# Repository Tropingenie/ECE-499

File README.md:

# ECE-499
[Nozzle Flow Control for Agricultural Integration](https://tropingenie.github.io/ECE-499-Website/)

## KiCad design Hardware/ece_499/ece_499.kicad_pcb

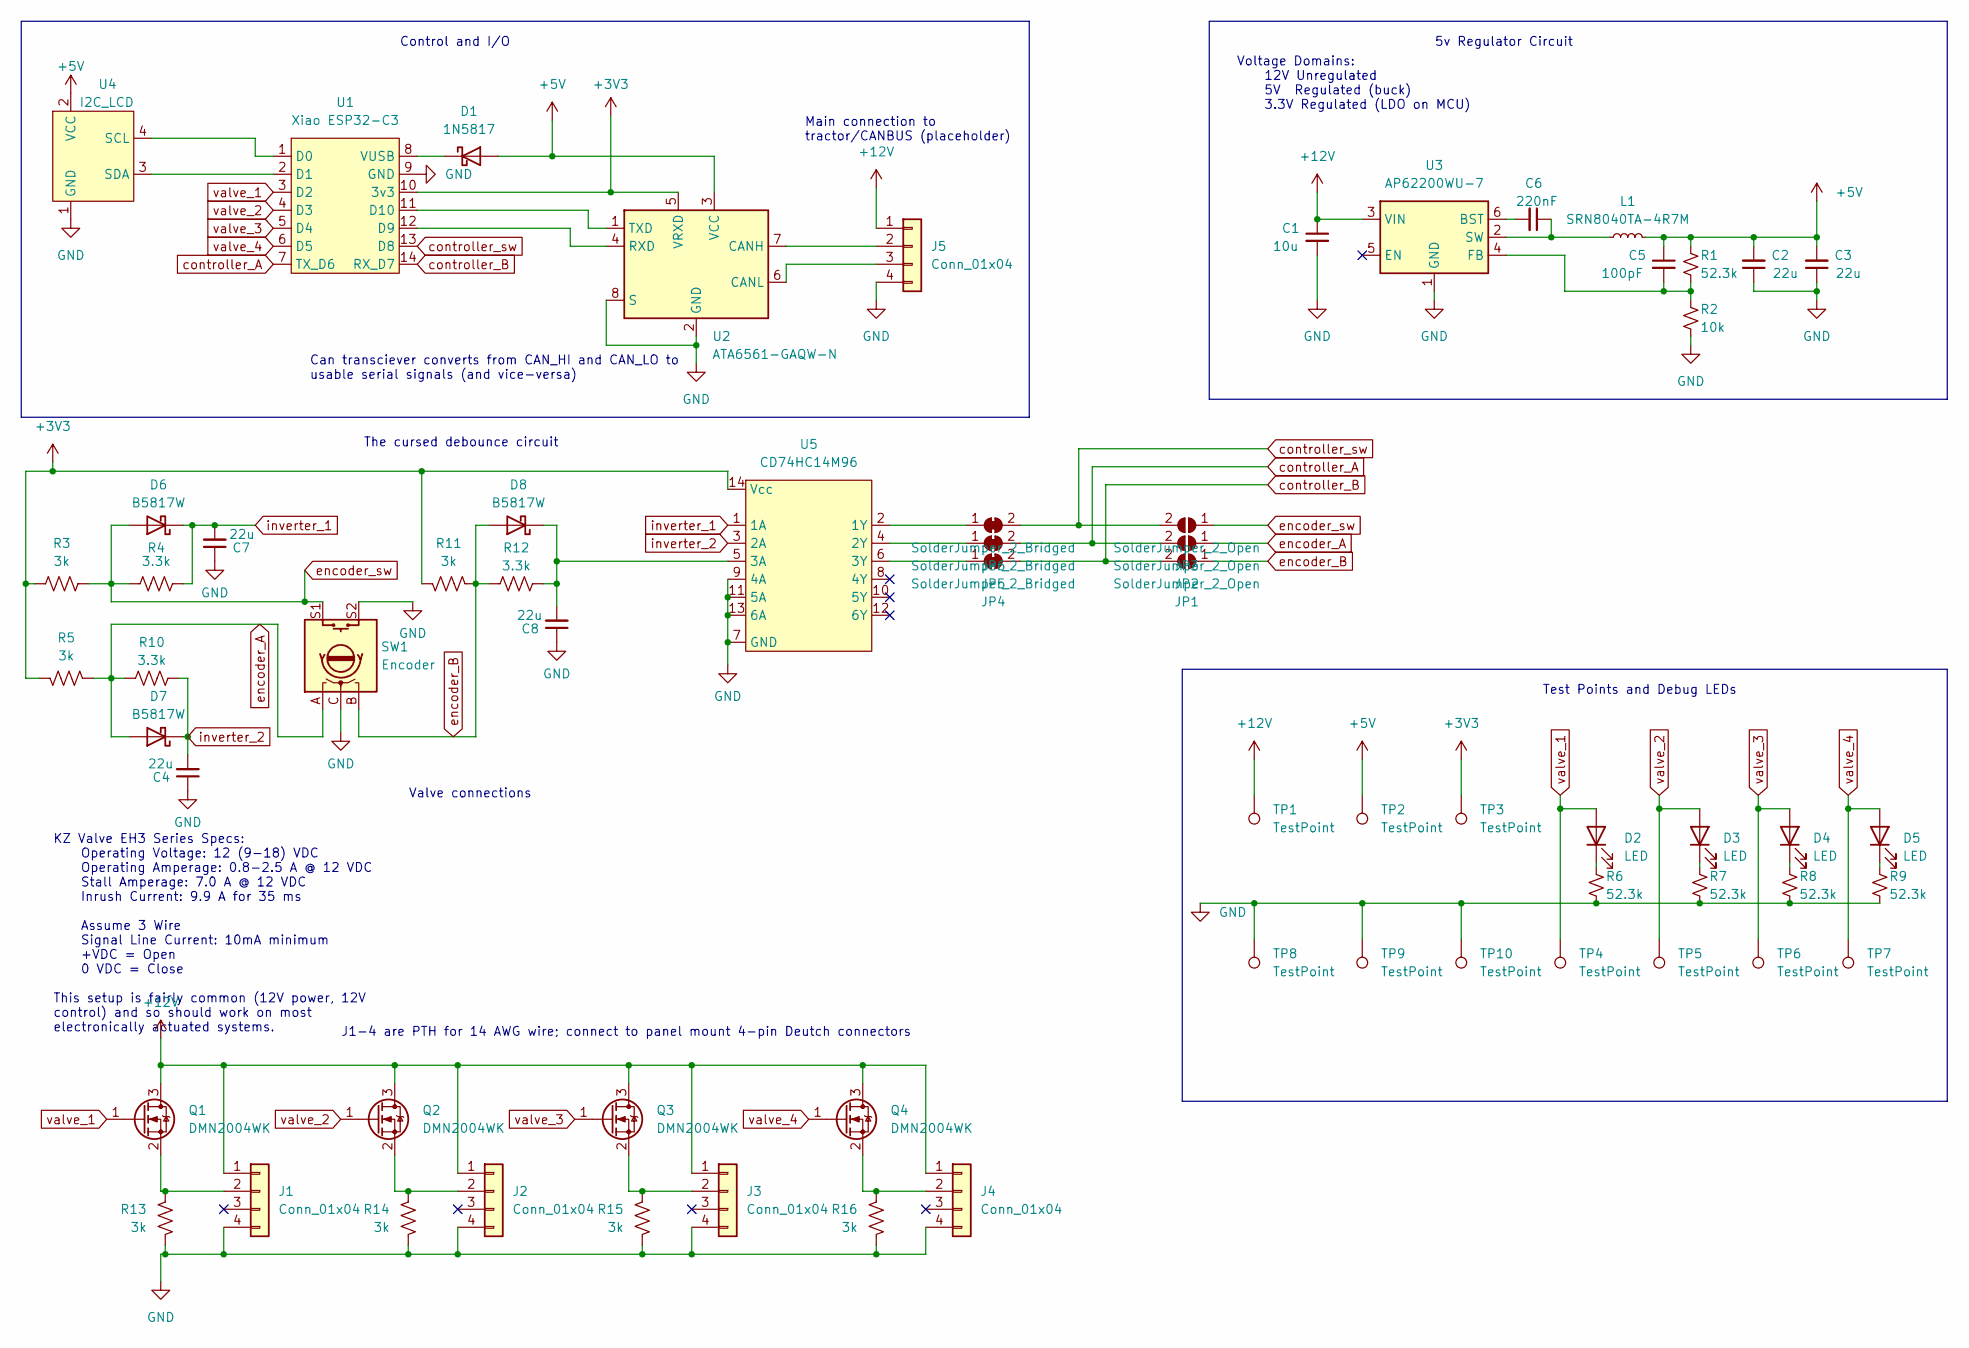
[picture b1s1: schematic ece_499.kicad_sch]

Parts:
C1: 10u; C_0805_2012Metric_Pad1.18x1.45mm_HandSolder
C2, C3, C4, C7, C8: 22u; C_0805_2012Metric_Pad1.18x1.45mm_HandSolder
C5: 100pF; C_0805_2012Metric_Pad1.18x1.45mm_HandSolder
C6: 220nF; C_0805_2012Metric_Pad1.18x1.45mm_HandSolder
D1: 1N5817; D_A-405_P7.62mm_Horizontal
D2, D3, D4, D5: LED; LED_D5.0mm
D6, D7, D8: B5817W; D_SOD-123
J1, J2, J3, J4, J5: Conn_01x04; 14 AWG 01x04
JP1, JP2, JP3: SolderJumper_2_Open; SolderJumper-2_P1.3mm_Open_RoundedPad1.0x1.5mm
JP4, JP5, JP6: SolderJumper_2_Bridged; SolderJumper-2_P1.3mm_Bridged2Bar_RoundedPad1.0x1.5mm
L1: SRN8040TA-4R7M; IND_SRN8040TA-4R7M
Q1, Q2, Q3, Q4: DMN2004WK; SOT-323_SC-70
R1: 52.3k; R_1206_3216Metric_Pad1.30x1.75mm_HandSolder
R2: 10k; R_1206_3216Metric_Pad1.30x1.75mm_HandSolder
R3, R5, R11, R13, R14, R15, R16: 3k; R_1206_3216Metric_Pad1.30x1.75mm_HandSolder
R4, R10, R12: 3.3k; R_1206_3216Metric_Pad1.30x1.75mm_HandSolder
R6, R7, R8, R9: 52.3k; R_Axial_DIN0204_L3.6mm_D1.6mm_P5.08mm_Horizontal
SW1: Encoder; PEC16-4015F-S0024
TP1, TP2, TP3, TP4, TP5, TP6, TP7, TP8, TP9, TP10: TestPoint; TestPoint_Pad_D2.0mm
U1: Xiao ESP32-C3; XIAO ESP32-C3
U2: ATA6561-GAQW-N; SOIC-8_3.9x4.9mm_P1.27mm
U3: AP62200WU-7; SOT-23-6_Handsoldering
U4: I2C_LCD; PinHeader_1x06_P1.00mm_Horizontal
U5: CD74HC14M96; SO-14_3.9x8.65mm_P1.27mm

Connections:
+3V3: R3.1, R5.1, R11.1, TP3.1, U1.10 (3v3), U2.5 (VRXD), U5.14 (Vcc)
+5V: C2.2, C3.2, C5.1, D1.2 (A), L1.2, R1.1, TP2.1, U2.3 (VCC), U4.2 (VCC)
+12V: C1.1, J1.1, J2.1, J3.1, J4.1, J5.1, Q1.3 (D), Q2.3 (D), Q3.3 (D), Q4.3 (D), TP1.1, U3.3 (VIN)
GND: C1.2, C2.1, C3.1, C4.1, C7.1, C8.1, J1.4, J2.4, J3.4, J4.4, J5.4, R2.2, R6.2, R7.2, R8.2, R9.2, R13.1, R14.1, R15.1, R16.1, SW1.C, SW1.S2, TP8.1, TP9.1, TP10.1, U1.9 (GND), U2.2 (GND), U2.8 (S), U3.1 (GND), U4.1 (GND), U5.7 (GND), U5.9 (4A), U5.11 (5A), U5.13 (6A)
unnamed: D1.1 (K), U1.8 (VUSB)
unnamed: D2.1 (K), R6.1
unnamed: D3.1 (K), R7.1
unnamed: D4.1 (K), R8.1
unnamed: D5.1 (K), R9.1
unnamed: C8.2, D8.1 (K), R12.1, U5.5 (3A)
unnamed: J1.2, Q1.2 (S), R13.2
unnamed: J2.2, Q2.2 (S), R14.2
unnamed: J3.2, Q3.2 (S), R15.2
unnamed: J4.2, Q4.2 (S), R16.2
unnamed: J5.2, U2.7 (CANH)
unnamed: J5.3, U2.6 (CANL)
unnamed: JP4.1 (A), U5.6 (3Y)
unnamed: JP5.1 (A), U5.4 (2Y)
unnamed: JP6.1 (A), U5.2 (1Y)
unnamed: U1.1 (D0), U4.4 (SCL)
unnamed: U1.2 (D1), U4.3 (SDA)
unnamed: U1.12 (D9), U2.4 (RXD)
unnamed: U1.11 (D10), U2.1 (TXD)
unnamed: C6.2, U3.6 (BST)
unnamed: C5.2, R1.2, R2.1, U3.4 (FB)
unnamed: C6.1, L1.1, U3.2 (SW)
controller_A: JP2.2 (B), JP5.2 (B), U1.7 (TX_D6)
controller_B: JP1.2 (B), JP4.2 (B), U1.14 (RX_D7)
controller_sw: JP3.2 (B), JP6.2 (B), U1.13 (D8)
encoder_A: D7.2 (A), JP2.1 (A), R5.2, R10.2, SW1.A
encoder_B: D8.2 (A), JP1.1 (A), R11.2, R12.2, SW1.B
encoder_sw: D6.2 (A), JP3.1 (A), R3.2, R4.2, SW1.S1
inverter_1: C7.2, D6.1 (K), R4.1, U5.1 (1A)
inverter_2: C4.2, D7.1 (K), R10.1, U5.3 (2A)
valve_1: D2.2 (A), Q1.1 (G), TP4.1, U1.3 (D2)
valve_2: D3.2 (A), Q2.1 (G), TP5.1, U1.4 (D3)
valve_3: D4.2 (A), Q3.1 (G), TP6.1, U1.5 (D4)
valve_4: D5.2 (A), Q4.1 (G), TP7.1, U1.6 (D5)

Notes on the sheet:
Valve connections
5v Regulator Circuit
KZ Valve EH3 Series Specs: Operating Voltage: 12 (9-18) VDC Operating Amperage: 0.8-2.5 A @ 12 VDC Stall Amperage: 7.0 A @ 12 VDC Inrush Current: 9.9 A for 35 ms Assume 3 Wire Signal Line Current: 10mA minimum +VDC = Open 0 VDC = Close This setup is fairly common (12V power, 12V control) and so sho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
Control and I/O
Voltage Domains: 12V Unregulated 5V Regulated (buck) 3.3V Regulated (LDO on MCU)
The cursed debounce circuit
Can transciever converts from CAN_HI and CAN_LO to usable serial signals (and vice-versa)
Main connection to tractor/CANBUS (placeholder)
J1-4 are PTH for 14 AWG wire; connect to panel mount 4-pin Deutch connectors
Test Points and Debug LEDs

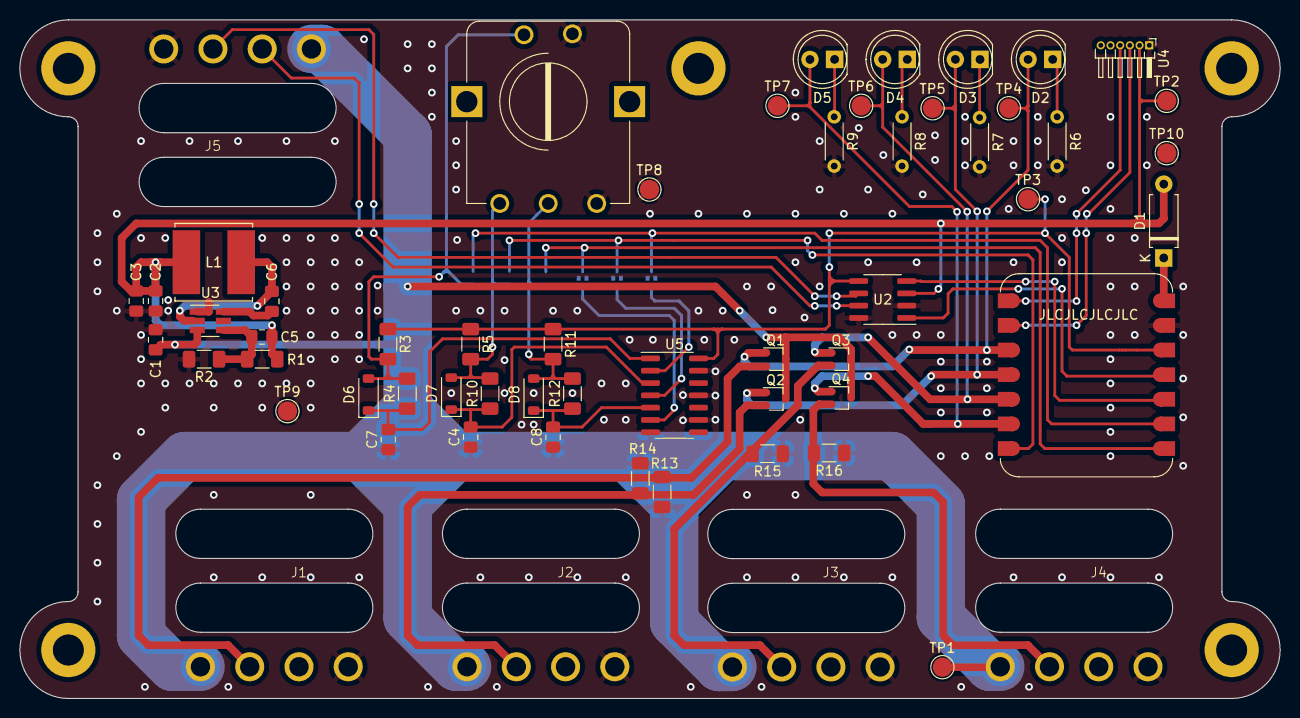
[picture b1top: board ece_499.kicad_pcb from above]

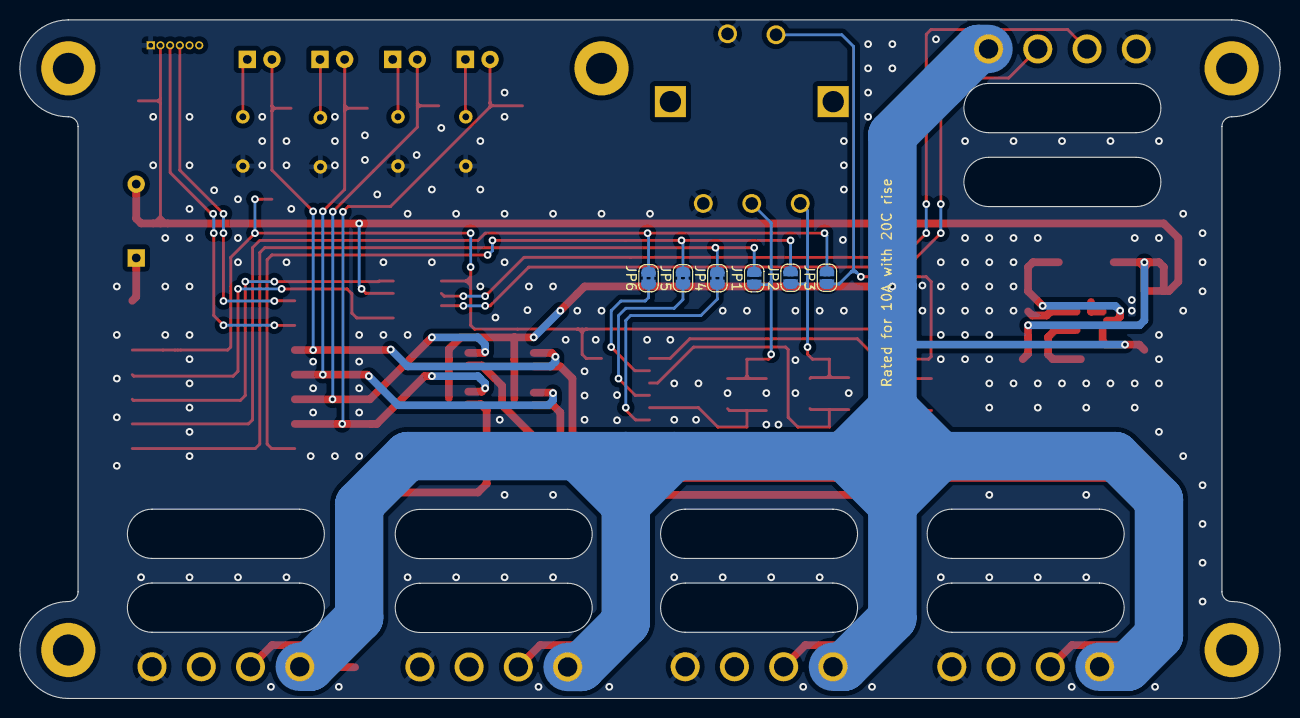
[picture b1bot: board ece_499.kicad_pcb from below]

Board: 2 copper layers, 130.0 x 70.0 mm, 64 parts (6 on the bottom side), 38 nets.

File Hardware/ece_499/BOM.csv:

"Reference","Value","Datasheet","Footprint","Qty","DNP"
"C1","10u","~","Capacitor_SMD:C_0805_2012Metric_Pad1.18x1.45mm_HandSolder","1",""
"C2,C3,C4,C7,C8","22u","~","Capacitor_SMD:C_0805_2012Metric_Pad1.18x1.45mm_HandSolder","5",""
"C5","100pF","~","Capacitor_SMD:C_0805_2012Metric_Pad1.18x1.45mm_HandSolder","1",""
"C6","220nF","~","Capacitor_SMD:C_0805_2012Metric_Pad1.18x1.45mm_HandSolder","1",""
"D1","1N5817","https://www.smc-diodes.com/propdf/B5817W-B5819W%20N1752%20REV.-.pdf","Diode_THT:D_A-405_P7.62mm_Horizontal","1",""
"D2,D3,D4,D5","LED","~","LED_THT:LED_D5.0mm","4",""
"D6,D7,D8","B5817W","https://www.smc-diodes.com/propdf/B5817W-B5819W%20N1752%20REV.-.pdf","Diode_SMD:D_SOD-123","3",""
"J1,J2,J3,J4,J5","Conn_01x04","~","Imported_Parts:14 AWG 01x04","5",""
"JP1,JP2,JP3","SolderJumper_2_Open","~","Jumper:SolderJumper-2_P1.3mm_Open_RoundedPad1.0x1.5mm","3",""
"JP4,JP5,JP6","SolderJumper_2_Bridged","~","Jumper:SolderJumper-2_P1.3mm_Bridged2Bar_RoundedPad1.0x1.5mm","3",""
"L1","SRN8040TA-4R7M","~","Imported_Parts:IND_SRN8040TA-4R7M","1",""
"Q1,Q2,Q3,Q4","DMN2004WK","https://www.diodes.com/assets/Datasheets/DMN2004WK.pdf","Package_TO_SOT_SMD:SOT-323_SC-70","4",""
"R1,R6,R7,R8,R9","52.3k","~","-- mixed values --","5",""
"R2","10k","~","Resistor_SMD:R_1206_3216Metric_Pad1.30x1.75mm_HandSolder","1",""
"R3,R5,R11,R13,R14,R15,R16","3k","~","Resistor_SMD:R_1206_3216Metric_Pad1.30x1.75mm_HandSolder","7",""
"R4,R10,R12","3.3k","~","Resistor_SMD:R_1206_3216Metric_Pad1.30x1.75mm_HandSolder","3",""
"SW1","Encoder","https://www.bourns.com/docs/Product-Datasheets/pec16.pdf","Imported_Parts:PEC16-4015F-S0024","1",""
"TP1,TP2,TP3,TP4,TP5,TP6,TP7,TP8,TP9,TP10","TestPoint","~","TestPoint:TestPoint_Pad_D2.0mm","10",""
"U1","Xiao ESP32-C3","","Imported_Parts:XIAO ESP32-C3","1",""
"U2","ATA6561-GAQW-N","https://www.ti.com/lit/ds/symlink/sn65hvd257.pdf","Package_SO:SOIC-8_3.9x4.9mm_P1.27mm","1",""
"U3","AP62200WU-7","https://www.diodes.com/assets/Datasheets/AP62200_AP62201_AP6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","Package_TO_SOT_SMD:SOT-23-6_Handsoldering","1",""
"U4","I2C_LCD","","Connector_PinHeader_1.00mm:PinHeader_1x06_P1.00mm_Horizontal","1",""
"U5","CD74HC14M96","https://www.ti.com/lit/ds/symlink/cd74hc14.pdf","Package_SO:SO-14_3.9x8.65mm_P1.27mm","1",""

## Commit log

2024-05-21 Initial hardware design considerations
2024-05-23 Continue components selection and setup
2024-05-24 Added parts
    -Created circuit for regulator
    -Wired up CAN transceiver
    -Added rotary encoder
    -Added I2C LCD interface
2024-05-25 stop being dumb
    -fixed 5v into switch and can transceiver
    -made the symbol less bad for the i2c
2024-05-28 Design connectors for connectors to actuators
2024-05-28 Add more test points
2024-05-30 Add debug LEDs to signal TPs
2024-05-30 Complete footprint selection
2024-05-30 Remove incorrect encoder footprint; add main CANBUS header
2024-06-03 Set up PEC16 footprint
2024-06-03 Validate footprints(corrected B5817W)
2024-06-03 Initial PCB setup part 1
2024-06-03 Initial PCB layout and fix reg schema
2024-06-05 Cursed debouncy :(
2024-06-06 Fix (?) debounce schema
2024-06-09 Add new encoder design to initial PCB layout
2024-06-09 5v reg circuit on PCB
2024-06-09 Implement 3v3 lines on PCB
2024-06-09 Implement encoder debouncer
2024-06-09 Encoder and CAN receiver traces
2024-06-11 CANBUS tranceiver traces
2024-06-11 clean up encoder traces
2024-06-11 clean up 3v3 trace
2024-06-11 Initial valve FET connections
2024-06-11 More valve FET -> connector
2024-06-12 Add pulldowns on valve FETs
2024-06-12 Add pulldowns to PCB
2024-06-12 Ground plane and start stitching vias
2024-06-12 More stitching vias
2024-06-12 Wire LCD header
2024-06-12 Run LED traces
2024-06-12 More vias, 3D model of PEC16
2024-06-12 fix resistor values, update datasheet
    -Fixed R1 values for debounce circuits
    -Changed all 2.7k resistors to 3k
    -Updated datasheet for DMN2004WK
2024-06-13 Moved testpoints
    -Moved the testpoints onto the board. All are on the front side of the board.
    -The zone boundaries are now an actual square.
2024-06-14 Minor fixes - Replace MCU diode with 1N5817 - Move 3v3 TP - Remove 90 degree traces - More stitching vias
2024-06-14 Export BOM for creating DigiKey order
2024-06-14 Run DRC - Validate footprints - Add thermal trace to reg - Move TP2 and TP10 to avoid overlapping silk - More stitching vias :)
2024-06-14 More vias, 3D models
    - More stitching vias
    - Add model for L1
2024-06-14 Touched kicad_pro file
2024-06-15 Mounting points - Add M3 mounting points - Clean up board edges - Validate manufacturing clearances
2024-06-15 Add dimensions to board file
2024-06-15 Add dimensions to board file part 2
2024-06-15 Add dimensions to board file part 3
2024-06-15 Hide SW1 silk
2024-06-15 Export Gerbers, update .gitignore
2024-06-22 Add SuperMini 3D model for screenshot
2024-07-05 Pull in software as submodule
2024-07-11 Pull in firmware as submodules
2024-07-19 Added enclosure design
2024-07-23 Add website to main repo
2024-07-27 additional enclosures
2024-07-27 added cleaned up version of schematic
2024-07-28 Add arduino firmware as submodule
2024-07-28 Fix arduino firmware path
2024-07-28 Actually add arduino firmware with correct path
2024-08-05 Updated enclosure fusion exports
2024-08-11 Update submodules to latest
2024-08-11 Add report/manufacturing outputs
2024-08-11 Switch firmware submodules to main branch
2024-08-11 Add webpage link to README
